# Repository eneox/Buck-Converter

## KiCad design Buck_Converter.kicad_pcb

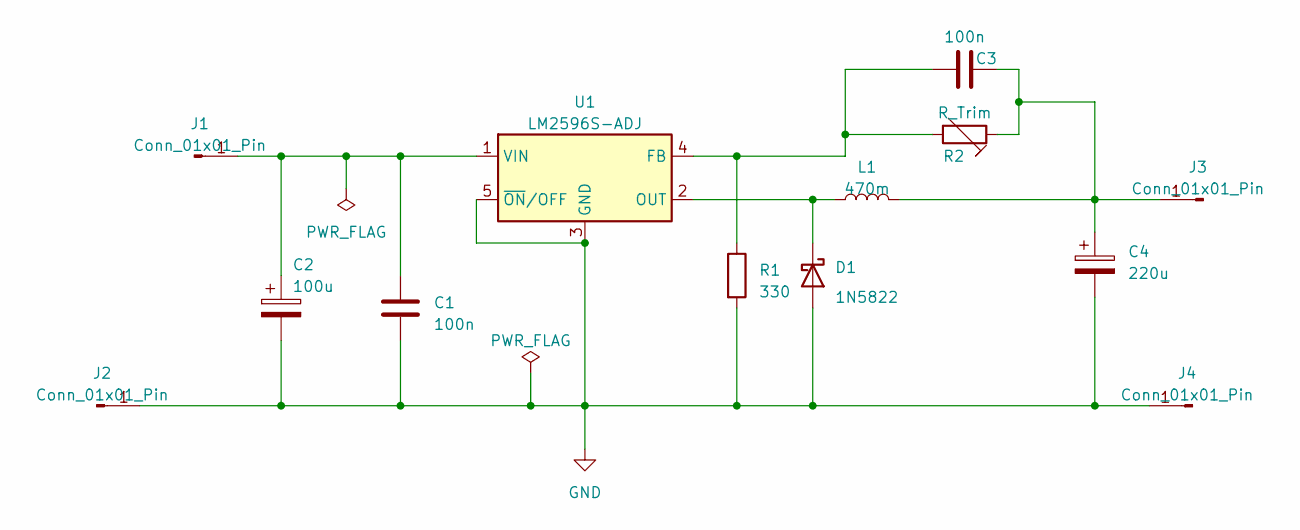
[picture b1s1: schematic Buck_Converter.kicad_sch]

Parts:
C1, C3: 100n; C_0603_1608Metric_Pad1.08x0.95mm_HandSolder
C2: 100u; CP_Elec_8x10
C4: 220u; CP_Elec_8x10
D1: 1N5822; D_1206_3216Metric
J1, J2, J3, J4: Conn_01x01_Pin; SolderWire-0.5sqmm_1x01_D0.9mm_OD2.1mm
L1: 470m; L_12x12mm_H6mm
R1: 330; R_0603_1608Metric_Pad0.98x0.95mm_HandSolder
R2: R_Trim; Potentiometer_Bourns_3296Y_Vertical
U1: LM2596S-ADJ; TO-263-5_TabPin3

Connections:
GND: C1.2, C2.2, C4.2, D1.2 (A), J2.1, J4.1, R1.2, U1.3 (GND), U1.5 (~ON/OFF)
unnamed: D1.1 (K), L1.1, U1.2 (OUT)
unnamed: C1.1, C2.1, J1.1, U1.1 (VIN)
unnamed: C3.2, C4.1, J3.1, L1.2, R2.1
unnamed: C3.1, R1.1, R2.2, U1.4 (FB)

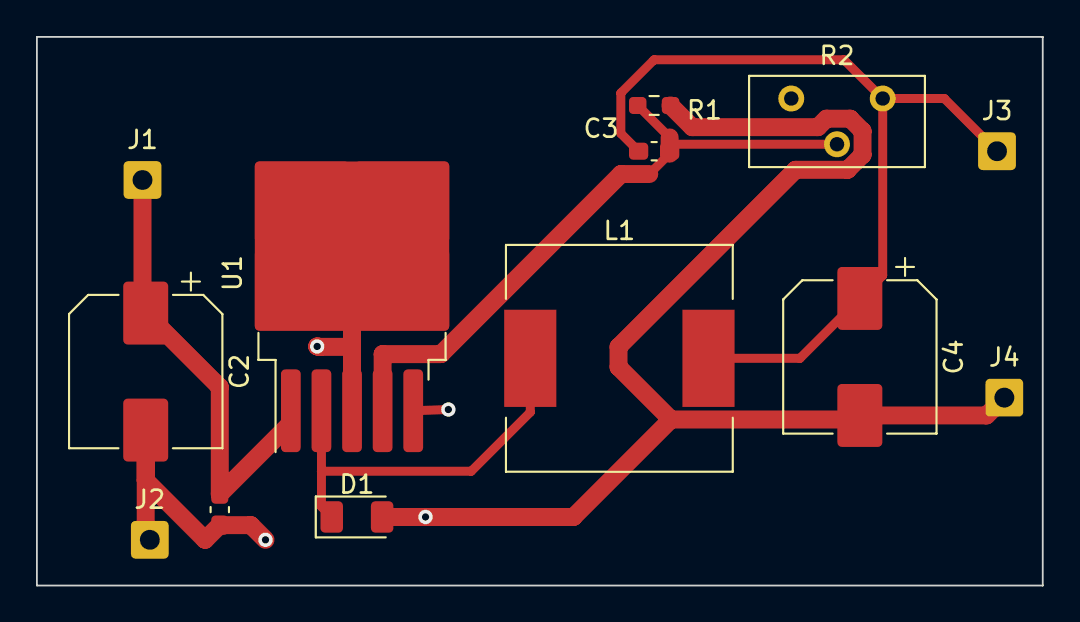
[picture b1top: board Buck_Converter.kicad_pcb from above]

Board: 2 copper layers, 55.9 x 30.5 mm, 13 parts (0 on the bottom side), 5 nets.

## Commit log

2023-04-29 Buck-Converter
